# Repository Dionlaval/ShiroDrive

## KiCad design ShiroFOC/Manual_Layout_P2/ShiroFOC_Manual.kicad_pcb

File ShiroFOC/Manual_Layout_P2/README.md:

# ShiroFOC P2 — manual layout starting point

Open **ShiroFOC_Manual.kicad_pro** in this folder, then its PCB. This is the new working revision. The prior P1 project and Manual_Rebuild files are preserved.

## What is carried forward

- P1's 80 × 80 mm rounded outline, four M3 mounting holes, bulk-capacitor row and parallel bridge/phase-output arrangement.
- Latest manual schematic and imported component libraries. U604 now uses standard SOT-23-6 with its generic model (TI DBV six-pin package, 0.95 mm pitch; standard KiCad lands are an IPC-style alternative to TI's example).
- Current footprint and net assignments, including the LR2512D Kelvin shunts. Source-reference changes such as U301 → U4 and Q401/Q402/Q403 → U1/U2/U3 are explicitly mapped.
- Four copper layers: 70 / 17.5 / 17.5 / 70 µm. The copied dielectric dimensions are provisional; they are not a confirmed fabrication stack or an impedance calculation.

This is **rough placement, intentionally unrouted**. Component shifts clear gross overlaps, not optimize every pin-local loop. Final placement, copper planes, routing, silkscreen and fabrication checks are the user's next steps. A guide box is not a copper zone or enforced keepout.

## Guide layers

| Layer | Content |
|---|---|
| Dwgs.User | Mechanical screw envelopes and routing reminders |
| User.1 | Bulk capacitors, three power cells and brake-stage regions |
| User.2 | Auxiliary supply, USB and external-interface regions |
| User.3 | MCU/analog area, centred underside encoder and sense-route direction hints |
| F.Fab / B.Fab | Component references and body outlines |

Hide the guide layers when they obstruct routing. Nothing on them is electrical copper.

## Placement and routing checklist

1. **Mechanics first:** retain the encoder centre on the back at (140,140) mm. The magnet is outside that face; no top-side central magnet void is required. Keep the MCU offset from the encoder to preserve space for underside decoupling. Check connector mating clearance and corner screw/washer envelopes; the circles show an 8 mm hardware envelope.
2. **Three repeated phase cells:** U1/U2/U3 line up with J1's U/V/W holes. Keep each VM ceramic → MOSFET pair → low-side shunt → ceramic ground loop short and broad. Respect the actual schematic: the three sets of local VM bypass capacitors return to GND. Do not copy older notes that put a capacitor above the shunt.
3. **Shunts:** active phase U/V/W shunts are R3/R1/R5 respectively, on the back near the power cells. Pads1/4 carry current; pads2/3 are the Kelvin pickup stubs. Route from the stubs as a close pair, away from phase/gate/brake switching nodes. Keep power pours from swallowing the stubs. Short direct force paths and multiple correctly sized vias are needed for backside shunts; there is no fixed amps-per-via guarantee.
4. **Gate drive:** finish placement around the actual U4 gate-driver pins before routing. Put R2/R4/R6 near the relevant GH gate pads. Pair the high-side drive with its source/phase return and low-side drive with its driver return. Bootstrap capacitors C4/C8/C12 are shown on the gate-driver sheet, between BOOTSTRAP1/2/3 and HS_RETURN_U/V/W. Place them at the driver pins. Route HS_RETURN directly to the corresponding MOSFET SH pad alongside the high-side gate trace; PHASE_U/V/W are separate high-current routes to the motor.
5. **Quiet measurement:** R417/R418/R419 and corresponding V/W networks, bias resistors and optional feedback capacitors belong close to their U4 amplifier pins. Use the underside of the MCU where useful, keeping clear of the encoder and hot power copper. Place VREF/VDDA filters and bypass capacitors close to their pins. Do not run main DC or brake return current through this area.
6. **Ground:** create substantially continuous GND planes on In1.Cu and In2.Cu. They provide signal return paths, not the sole motor-current conductor. Use broad outer-layer VM/GND paths for power. Stitch local decoupling grounds and signal layer transitions to the planes. Check both inner layers for accidental slots caused by via fields. A VM thermal via must not touch GND; likewise the source above each shunt is not GND.
7. **Brake:** keep the external resistor connector and chopper loop at the edge, away from the encoder. Finish Q501/U501 placement and gate loop before signal routing. Keep BRK_SW copper compact and sense the bus from a quieter pickup.
8. **Supplies:** current topology is VM → LMR36510/U201 + L201 → 10V → MPM3620A/U205 → 5V mux → 3V3 LDO. U4 uses external VCC; there is no L301 internal-switcher inductor. Finish capacitor placement at U201 and U205 first, then keep feedback resistors away from switching copper. U205's embedded footprint keepout remains present.
9. **Interfaces:** AS5047 uses dedicated SPI; BMI323 uses I2C. Keep both over continuous ground. Place external Hall protection/buffer and U604 sensor-power protector near J601; place their decouplers at their pins. CAN protection belongs at the connectors, with JP801 termination access. USB D+/D− should be short and paired; determine 90Ω geometry from a real stack before treating the saved width/gap as final.
10. **Comparison part:** R7 is the disconnected BVR4026 parked outside the outline. Compare it to the small shunts and then remove it before production exports. DNP/excluded-from-BOM does not remove its copper/paste from Gerbers.

## Saved routing presets

- Global copper clearance / minimum track width: 0.15 mm.
- Default logic: 0.25 mm track, 0.20 mm clearance.
- Analog: 0.20 mm track/clearance. Gate: 0.40 mm initial width. Logic power: 0.50 mm initial width.
- Power class: 0.50 mm clearance target; its 2 mm track width is a router convenience, **not a 25 A current-rating calculation**. Use purpose-sized copper.
- Through vias: 0.60 / 0.30 mm default; 0.45 / 0.20 mm compact. No blind/buried or microvia plan.
- Copper-to-edge: 0.50 mm. Drill spacing: 0.20 mm base; 0.45 mm for pairs involving component pads, with a retained explicit U901 thermal-via exception.
- Silkscreen: 1.0 mm minimum text / 0.15 mm stroke / 0.20 mm clearance. Imported library reference styling is not final production silkscreen.

See `review/` for the native ERC, unrouted-board DRC, footprint/pad-net validation and migration manifest. Those checks establish a usable starting project, not a finished-board release. Remaining fast-overcurrent-trip, thermal and shunt reflow-profile questions carry forward from the manual schematic review and firmware requirements.

## Known starting-state flags

See [open items](review/OPEN_ITEMS.md): U204's imported land pattern has 0.10 mm copper gaps, U901 has 0.15 mm thermal-via hole webs, and U205 has two NC/test symbol pins without footprint pads. These are recorded rather than hidden by relaxed rules. The board is ready for manual placement/routing work, not fabrication.

## Optional brake NTC — 27 September 2026

J502 is the new **bottom-side, left-edge** JST GH two-pin connector: **1 = NTC, 2 = GND**. Use an electrically insulated 10 kΩ-at-25°C probe on the external brake resistor; configure its actual temperature curve and rating. R511 is the 10 kΩ pull-up. R512/C505/D505 form the series filter and rail clamps beside U4 on the back. Keep the unfiltered probe net away from switching copper; route its dedicated ground back to the quiet ground plane, not through the brake-current return. No new routing has been added.

PC2 / U4 pad 11 is now `NTC_BRAKE` / ADC12_IN8. The status LED moved to PC15 / pad 5 with R304 = 2.2 kΩ; TP1021 is now labelled `STATUS_LED_N`. Existing footprint placement is preserved. Use the updated [firmware requirements](../requirements/FIRMWARE_REQUIREMENTS.md); old firmware that drives PC2 as an LED output is incompatible.

See [addition notes and checks](review/brake_ntc/README.md). `review/brake_ntc/before.zip` preserves the project files from before this addition. The older Manual_Rebuild project remains unchanged.

## Bootstrap return correction — 27 September 2026

The latest saved user placement is retained. C4/C8/C12 now appear on the gate-driver schematic sheet, connected between each BOOTSTRAP pin and its OUTx/SH return. `HS_RETURN_U/V/W` belong to the Gate class; `PHASE_U/V/W` belong to the Power class. Keep these PCB routes separate: they join inside the dual-MOSFET package. Capacitor values and footprints are unchanged.

The five NTC components also have corrected hierarchy paths and restored references J502/R511/R512/C505/D505. See [current verification](review/bootstrap_return/README.md).

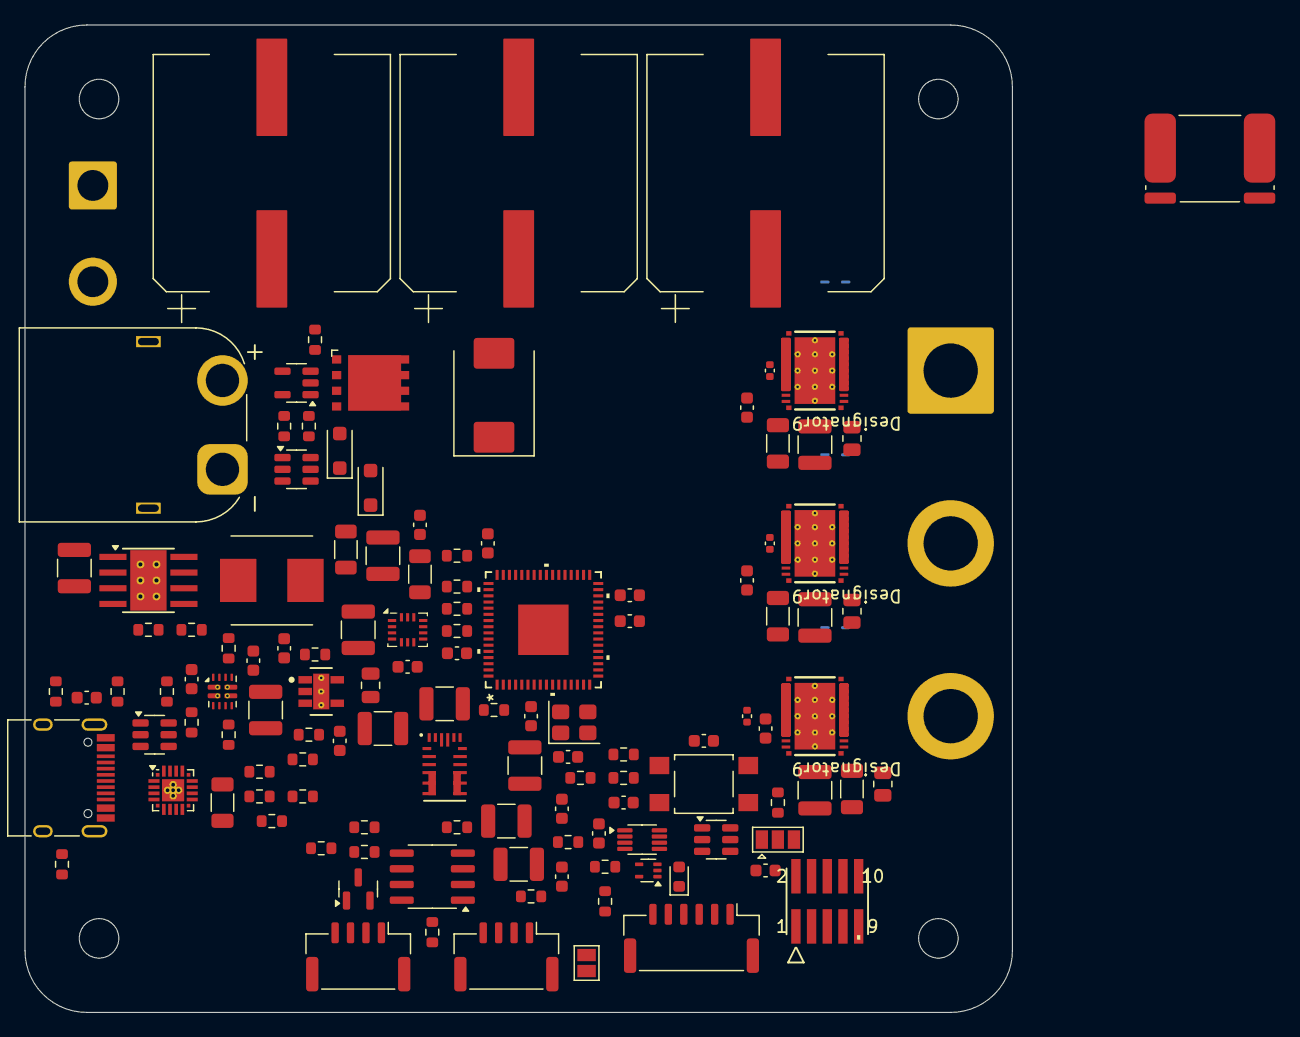
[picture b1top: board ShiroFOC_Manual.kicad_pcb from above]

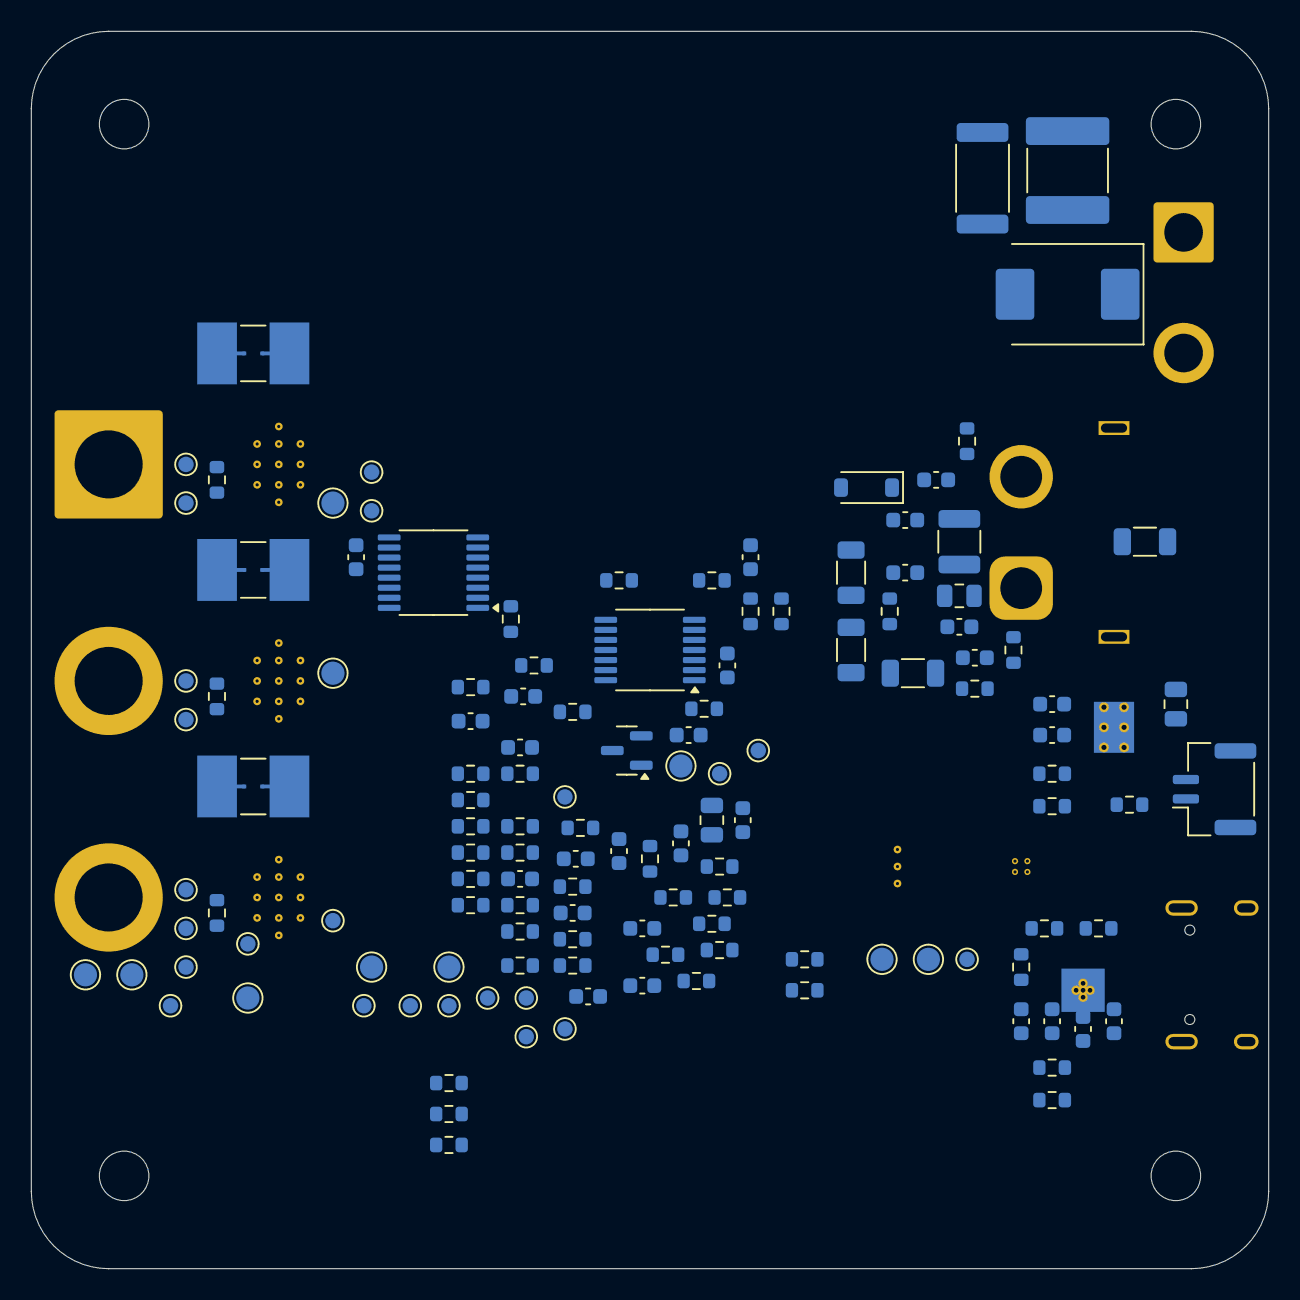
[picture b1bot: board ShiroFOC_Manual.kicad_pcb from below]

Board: 4 copper layers, 80.0 x 80.0 mm, 260 parts (132 on the bottom side), 145 nets, no tracks yet.

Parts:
C1, C5, C9: 10nF; C_0402_1005Metric
C2, C6, C10: 1uF; C_1206_3216Metric
C3, C7, C11: 4.7uF; C_1210_3225Metric
C4, C8, C12: 220nF; C_0603_1608Metric
C101, C102, C103: 680uF 63V; Panasonic_EEVFK_K16_18x16.5
C104: 4.7uF 100V X7R; C_1210_3225Metric
C105: 100nF 100V X7R; C_0805_2012Metric
C106: 10nF 100V C0G; C_0603_1608Metric
C107: RC DAMP C - TUNE; C_2220_5750Metric
C108, C314, C711, C712, C713: 10nF; C_0603_1608Metric
C201: 2.2uF 100V X7R; C_1210_3225Metric
C202: 220nF 100V X7R; C_0805_2012Metric
C203, C209, C211, C301, C303, C305, C307, C310, C601, C603, C605, C701, C702, C801, C902, C904: 100nF; C_0603_1608Metric
C204, C304, C306, C602, C802: 1uF; C_0603_1608Metric
C205, C206, C214, C215: 22uF 25V X7R; C_1210_3225Metric
C207: 4.7nF 2kV; C_1206_3216Metric
C208: 1uF 10V; C_0603_1608Metric
C210: 22uF 10V X7R; C_1210_3225Metric
C212, C213: 2.2uF 10V X7R; C_0603_1608Metric
C218, C219: 22uF 16V X7R; C_1210_3225Metric
C302: 10uF 10V; C_0805_2012Metric
C308, C309: 10pF C0G; C_0603_1608Metric
C311: 220nF 100V; C_0805_2012Metric
C312: 10uF 25V X7R; C_1210_3225Metric
C313: 100nF 25V; C_0603_1608Metric
C414, C424, C434: 47pF C0G; C_0603_1608Metric
C501: 1uF 25V; C_0603_1608Metric
C502, C503, C604: 100nF 50V; C_0603_1608Metric
C504: 1nF C0G; C_0603_1608Metric
C505: 100nF 16V; C_0603_1608Metric
C606: 4.7uF 16V X7R; C_0603_1608Metric
C607: 100nF 16V X7R; C_0603_1608Metric
C901, C903: 4.7uF 10V; C_0603_1608Metric
D101: VM TVS - SELECT AFTER TEST; D_SMC
D301: RED; LED_0603_1608Metric
D501: BZT52C12 12V; D_SOD-123
D502, D503: BAT54H; D_SOD-123F
D504: B5100C 100V 5A; D_SMC
D505: BAT54S; SOT-23
D601: TPD3E001DRLR 3-line ESD; TPD3E001_DRL5
D801: PESD2CANFD24V-T; SOT-23
H1, H2, H3, H4: M3 NPTH; MountingHole_3.2mm_M3
J1: MOTOR U/V/W; SolderWire-6sqmm_1x03_P14mm_D3.5mm_OD7mm
J101: AMASS XT60PW-M; AMASS_XT60PW-M_1x02_P7.20mm_Horizontal
J201: USB-C service; USB_C_Receptacle_HRO_TYPE-C-31-M-12
J501: BRAKE RESISTOR; SolderWire-2sqmm_1x02_P7.8mm_D2mm_OD3.9mm
J502: BRAKE NTC; JST_GH_SM02B-GHS-TB_1x02-1MP_P1.25mm_Horizontal
J601: EXT ENCODER / HALL; JST_GH_BM06B-GHS-TBT_1x06-1MP_P1.25mm_Vertical
J801: CAN 1; JST_GH_BM04B-GHS-TBT_1x04-1MP_P1.25mm_Vertical
J802: CAN 2; JST_GH_BM04B-GHS-TBT_1x04-1MP_P1.25mm_Vertical
J1001: ARM Cortex SWD 10-pin; FTSH_105_01_L_DV_K
JP601: SENSOR SUPPLY; SolderJumper-3_P1.3mm_Open_Pad1.0x1.5mm
JP801: TERM ENABLE; SolderJumper-2_P1.3mm_Open_Pad1.0x1.5mm
L201: 47uH / 1.9A; WE_LHMI_7050_74437349470
Q501: CSD19531Q5A 100V; CSD19531Q5A_Q5A_DQJ0008A
R1, R3, R5: 0.5m 1%; R_Shunt_LR2512D_0m5_3W_Kelvin
R2, R4, R6: 4R7; R_0805_2012Metric
R7: BVR 0.5m 1% (DNP); R_Shunt_Isabellenhuette_BVR4026
R101: 470k 0.25W; R_1206_3216Metric
R102: RC DAMP R - TUNE; R_2512_6332Metric
R103, R104: 270k 0.1% 100V; R_1206_3216Metric
R105: 27k 0.1%; R_0603_1608Metric
R106, R312, R711, R712, R713, R901: 1k; R_0603_1608Metric
R201: 100k 1%; R_0603_1608Metric
R202: 11.1k 1%; R_0603_1608Metric
R203, R204: 5.1k; R_0603_1608Metric
R205, R301, R302: 0R; R_0603_1608Metric
R206: 15.0k 1%; R_0603_1608Metric
R207, R209, R211, R213: 5.10k 1%; R_0603_1608Metric
R208: 10.0k 1%; R_0603_1608Metric
R210, R212: 22.0k 1%; R_0603_1608Metric
R214: 80.6k 1%; R_0603_1608Metric
R215, R305, R306, R307, R309, R311, R501, R504, R505, R604, R801, R805: 10k; R_0603_1608Metric
R216: 34.0k 0.1%; R_0603_1608Metric
R217: 6.49k 0.1%; R_0603_1608Metric
R218, R219, R303, R310, R615, R616, R617: 100k; R_0603_1608Metric
R304, R308, R715: 2.2k; R_0603_1608Metric
R313, R314: 22R; R_0603_1608Metric
R410, R420, R430, R441, R442, R443: 56k 0.1%; R_0603_1608Metric
R417, R418, R427, R428, R437, R438: 1k 0.1%; R_0603_1608Metric
R419, R429, R439: 28k 0.1%; R_0603_1608Metric
R502, R611: 33R; R_0603_1608Metric
R503: 4.7R; R_0603_1608Metric
R506, R507, R508: 150k 0.1% 200V; R_1206_3216Metric
R509: 12.7k 0.1%; R_0603_1608Metric
R510: 1M 0.1%; R_0603_1608Metric
R511: 10k 1%; R_0603_1608Metric
R512, R701, R702, R703: 4.7k 1%; R_0603_1608Metric
R605, R606, R607, R902, R903: 100R; R_0603_1608Metric
R608, R609, R610: 4.7k DNP; R_0603_1608Metric
R802: 120R 1%; R_0603_1608Metric
R803: 0R CANH link; R_0603_1608Metric
R804: 0R CANL link; R_0603_1608Metric
R904: 22.1k 1%; R_0603_1608Metric
R905: 47.5k 1%; R_0603_1608Metric
SW301: RESET; SW_SPST_TL3305A
TH701, TH702, TH703: 10k NTC B3380; R_0603_1608Metric
TP101: VM; TestPoint_Pad_D1.5mm
TP102: GND; TestPoint_Pad_D1.5mm
TP103: VBUS_SENSE; TestPoint_Pad_D1.5mm
TP201: PWR_SOURCE_STATUS; TestPoint_Pad_D1.5mm
TP202: 5V_USB; TestPoint_Pad_D1.5mm
TP301: VCC; TestPoint_Pad_D1.5mm
TP302: SCREF; TestPoint_Pad_D1.5mm
TP303: NRST; TestPoint_Pad_D1.5mm
TP501: BRAKE_GATE; TestPoint_Pad_D1.5mm
TP502: BRAKE_SWITCH; TestPoint_Pad_D1.5mm
TP701: NTC_PHASE_A; TestPoint_Pad_D1.0mm
TP702: NTC_PHASE_B; TestPoint_Pad_D1.0mm
TP703: NTC_PHASE_C; TestPoint_Pad_D1.0mm
TP901: USB_UART_TX; TestPoint_Pad_D1.0mm
TP902: USB_UART_RX; TestPoint_Pad_D1.0mm
TP1005: 5V_SYS; TestPoint_Pad_D1.0mm
TP1006: 3V3; TestPoint_Pad_D1.0mm
TP1008: SWDIO; TestPoint_Pad_D1.0mm
TP1009: SWCLK; TestPoint_Pad_D1.0mm
TP1010: ENC_SPI_CLK; TestPoint_Pad_D1.0mm
TP1011: SPI3_MISO; TestPoint_Pad_D1.0mm
TP1012: ENC_SPI_MOSI; TestPoint_Pad_D1.0mm
TP1013: FDCAN1_TX; TestPoint_Pad_D1.0mm
TP1014: FDCAN1_RX; TestPoint_Pad_D1.0mm
TP1015: FEEDBACK_A_H1; TestPoint_Pad_D1.0mm
TP1016: FEEDBACK_B_H2; TestPoint_Pad_D1.0mm
TP1018: OPO_U1; TestPoint_Pad_D1.0mm
TP1019: OPO_V1; TestPoint_Pad_D1.0mm
TP1020: OPO_W1; TestPoint_Pad_D1.0mm
TP1021: SPARE_GPIO_1; TestPoint_Pad_D1.0mm
TP1022: CAN_STB; TestPoint_Pad_D1.0mm
TP1023: EXT_SENSOR_FAULT_N; TestPoint_Pad_D1.0mm
TP1024: I2C2_SDA; TestPoint_Pad_D1.0mm
U1, U2, U3: CSD88599Q5DC; DMM0022A
U4: STSPIN32G4; QFN_IN32G4_STM
U201: LMR36510FADDAR; LMR36510_DDA
U202: USBLC6-2SC6; USBLC6_SOT23_6
U203: TPS2121RUXR; TPS2121_RUX
U204: TLV75533PDYDR; TLV75533_DYD_GND
U205: MPM3620AGQV-Z; IC18_MPM3620AGQV-Z_MNP
U501: UCC27517ADBVR; UCC27517A_DBV5
U502: TLV3012BIDBVR; SOT-23-6
U601: AS5047P-ATSM; AS5047P_TSSOP14
U602: TMUX1574PW; TMUX1574_PW16
U603: 74LVC3G17; VSSOP-8_2.3x2mm_P0.5mm
U604: TPS2553DBVR; SOT-23-6
U701: BMI323; BMI323_LGA14
U801: TCAN3413DR; SOIC-8_3.9x4.9mm_P1.27mm
U901: CP2102N-A02-GQFN20; SiliconLabs_QFN-20-1EP_3x3mm_P0.5mm_EP1.8x1.8mm_ThermalVias
Y301: 24MHz 7pF; Crystal_SMD_3225-4Pin_3.2x2.5mm

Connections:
3V3: C213.1, C301.1, C302.1, C307.1, C503.1, C601.1, C602.1, C603.1, C605.1, C701.1, C702.1, C801.1, C802.1, C901.1, C902.1, C903.1, C904.1, D505.2 (K), J1001.1, JP601.1 (A), R215.1, R301.1, R303.1, R304.1, R305.1, R308.1, R309.1, R310.1, R511.1, R604.1, R701.1, R702.1, R703.1, R715.1, R801.1, R805.1, R901.1, TP1006.1, U4.1 (REG3V3/VDD), U4.2 (VBAT), U4.64 (REGIN), U204.5 (OUT), U502.6 (VDD), U601.11 (VDD), U601.12 (VDD3V3), U602.16 (VDD), U603.8 (VCC), U701.5 (VDDIO), U701.8 (VDD), U701.12 (CSB), U801.3 (VCC), U801.5 (VIO), U901.6 (VDD), U901.7 (VREGIN)
5V_BAT: C218.1, C219.1, R206.1, R210.1, R216.1, U203.7 (IN1), U205.7 (OUT), U205.8 (OUT), U205.9 (OUT)
5V_SYS: C210.1, C211.1, C212.1, JP601.3 (B), TP1005.1, U203.1 (OUT), U203.8 (OUT), U204.1 (IN), U204.3 (EN)
5V_USB: C208.1, R205.2, R208.1, R212.1, TP202.1, U203.2 (IN2)
5V_USB_RAW: J201.A4 (VBUS), J201.A9 (VBUS), J201.B4 (VBUS), J201.B9 (VBUS), R205.1, R904.1, U202.5 (VBUS)
/5 V / 3.3 V power/10V_FB: R201.2, R202.1, U201.5 (FB)
/5 V / 3.3 V power/10V_GOOD: R218.2, R219.1, U201.4 (PG), U205.17 (EN)
/5 V / 3.3 V power/U205_AGND: R217.2, U205.3 (AGND)
/5 V / 3.3 V power/U205_SW: U205.4 (SW), U205.5 (SW), U205.6 (SW)
/Brake chopper/BRAKE_NTC_RAW: J502.1, R511.2, R512.1
/Brake chopper/BRAKE_OV_CMD: D503.2 (A), R510.1, U502.1 (OUT)
/Brake chopper/BRAKE_PWM_DRV: D502.1 (K), D503.1 (K), R505.1, U501.3 (IN+)
/CAN interface/CANH_BUS: D801.1 (CANH_IN), J801.3, J802.3, R802.1, R803.2
/CAN interface/CANH_INT: R803.1, U801.7 (CANH)
/CAN interface/CANL_BUS: D801.2 (CANL_IN), J801.2, J802.2, JP801.2, R804.2
/CAN interface/CANL_INT: R804.1, U801.6 (CANL)
/CAN interface/CAN_SHIELD: J801.4, J802.4
/CAN interface/CAN_TERM_MID: JP801.1, R802.2
/Current / temperature/NTC_A_RAW: R701.2, R711.1, TH701.1
/Current / temperature/NTC_B_RAW: R702.2, R712.1, TH702.1
/Current / temperature/NTC_C_RAW: R703.2, R713.1, TH703.1
/Current / temperature/OPN_U1: C414.2, R418.2, R419.2, U4.16 (-)
/Current / temperature/OPN_V1: C424.2, R428.2, R429.2, U4.22 (-)
/Current / temperature/OPN_W1: C434.2, R438.2, R439.2, U4.25 (-)
/Current / temperature/OPP_U1: R410.2, R417.2, R441.1, U4.14 (+)
/Current / temperature/OPP_V1: R420.2, R427.2, R442.1, U4.20 (+)
/Current / temperature/OPP_W1: R430.2, R437.2, R443.1, U4.23 (+)
/External feedback/EXT_SUPPLY_SELECTED: C606.1, JP601.2 (C), U604.1 (IN), U604.3 (EN), U604.5 (ILIM)
/External feedback/EXT_VCC: C607.1, J601.1, R608.1, R609.1, R610.1, U604.6 (OUT)
/External feedback/FB_ESD_RAIL: C604.1, D601.5 (VCC)
/MCU / clock / SWD/NRST: C310.1, J1001.10, R303.2, SW301.1, TP303.1, U4.8 (PG10/NRST)
/MCU / clock / SWD/STATUS_LED_N: D301.1 (K), TP1021.1, U4.5 (PC15)
/USB service/CP2102_RST_N: R901.2, U901.9 (RST)
/USB service/CP2102_VBUS_SENSE: R904.2, R905.1, U901.8 (VBUS)
/USB service/UART_BRIDGE_RX: R903.2, U901.17 (RXD)
/USB service/UART_BRIDGE_TX: R902.1, U901.18 (TXD)
/USB service/USB_CC1: J201.A5 (CC1), R203.1
/USB service/USB_CC2: J201.B5 (CC2), R204.1
/USB service/USB_DM: U202.6 (IO1), U901.5 (D-)
/USB service/USB_DM_CONN: J201.A7 (D-), J201.B7 (D-), U202.1 (IO1)
/USB service/USB_DP: U202.4 (IO2), U901.4 (D+)
/USB service/USB_DP_CONN: J201.A6 (D+), J201.B6 (D+), U202.3 (IO2)
/USB service/USB_SHIELD: C207.1, J201.S1 (SHIELD)
AS5047P_CS_N: R309.2, U4.51 (PA15), U601.1 (CSn)
BOOTSTRAP1: C4.2, U4.41 (BOOTSTRAP1)
BOOTSTRAP2: C8.2, U4.38 (BOOTSTRAP2)
BOOTSTRAP3: C12.2, U4.35 (BOOTSTRAP3)
BRAKE_PWM: R501.1, R502.1, U4.60 (PB9)
CAN_STB: R801.2, TP1022.1, U4.28 (PB10), U801.8 (STB)
EXT_FEEDBACK_SELECT: R306.1, U4.53 (PD2), U602.1 (SEL)
EXT_SENSOR_FAULT_N: R604.2, TP1023.1, U4.3 (PC13), U604.4 (~FAULT)
FDCAN1_RX: TP1014.1, U4.47 (PA11), U801.4 (RXD)
FDCAN1_TX: R805.2, TP1013.1, U4.48 (PA12), U801.1 (TXD)
FEEDBACK_A_H1: TP1015.1, U4.57 (PB6), U602.4 (D1)
FEEDBACK_B_H2: TP1016.1, U4.58 (PB7), U602.7 (D2)
FEEDBACK_I_H3: R307.1, U4.59 (PB8/BOOT0), U602.9 (D3)
GHS1: R2.2, U4.43 (GHS1)
GHS2: R4.2, U4.40 (GHS2)
GHS3: R6.2, U4.37 (GHS3)
GLS1: U1.22 (GL), U4.29 (GLS1)
GLS2: U2.22 (GL), U4.30 (GLS2)
GLS3: U3.22 (GL), U4.31 (GLS3)
GND: C1.2, C2.2, C3.2, C5.2, C6.2, C7.2, C9.2, C10.2, C11.2, C101.2, C102.2, C103.2, C104.2, C105.2, C106.2, C107.2, C108.2, C201.2, C202.2, C204.2, C205.2, C206.2, C207.2, C208.2, C209.2, C210.2, C211.2, C212.2, C213.2, C214.2, C215.2, C218.2, C219.2, C301.2, C302.2, C303.2, C304.2, C305.2, C306.2, C307.2, C308.2, C309.2, C310.2, C311.2, C312.2, C313.2, C314.2, C501.2, C502.2, C503.2, C504.2, C505.2, C601.2, C602.2, C603.2, C604.2, C605.2, C606.2, C607.2, C701.2, C702.2, C711.2, C712.2, C713.2, C801.2, C802.2, C901.2, C902.2, C903.2, C904.2, D101.2 (A), D501.2 (A), D505.1 (A), D601.3 (GND), D801.3 (GND), J101.1, J201.A1 (GND), J201.A12 (GND), J201.B1 (GND), J201.B12 (GND), J502.2, J601.2, J801.1, J802.1, J1001.3, J1001.5, J1001.9, Q501.1 (S), Q501.2 (S), Q501.3 (S), R1.4 (POWER-), R3.4 (POWER-), R5.4 (POWER-), R101.2, R105.2, R202.2, R203.2, R204.2, R207.2, R209.2, R211.2, R213.2, R214.2, R219.2, R306.2, R307.2, R311.2, R441.2, R442.2, R443.2, R501.2, R504.2, R505.2, R509.2, R615.2, R616.2, R617.2, R905.2, SW301.2, TH701.2, TH702.2, TH703.2, TP102.1, U4.32 (PGND), U4.65 (VSS/EP), U201.1 (PGND), U201.9 (GND), U202.2 (GND), U203.12 (GND), U204.2 (GND), U205.12 (PGND), U205.13 (PGND), U205.14 (PGND), U501.2 (GND), U501.4 (IN-), U502.2 (GND), U601.5 (TEST), U601.13 (GND), U602.2 (S1A), U602.5 (S2A), U602.8 (GND), U602.11 (S3A), U603.4 (GND), U604.2 (GND), U701.1 (SDO/SA0), U701.6 (GNDIO), U701.7 (GND), U801.2 (GND), U901.3 (GND), U901.12 (GND), U901.21 (EP), Y301.2, Y301.4
I2C2_SCL: R308.2, U4.21 (PC4), U701.13 (SCK/SCL)
I2C2_SDA: R715.2, TP1024.1, U4.44 (PA8), U701.14 (SDI/SDA)
IMU_INT1: U4.17 (PA4), U701.4 (INT1)
IMU_INT2: U4.18 (PA5), U701.9 (INT2)
INPUT_MUX_ENABLE_N: R305.2, U4.4 (PC14), U602.15 (EN_N)
NTC_BRAKE: C505.1, D505.3 (COM), R512.2, U4.11 (PC2)
NTC_PHASE_A: C711.1, R711.2, TP701.1, U4.12 (PC3)
NTC_PHASE_B: C712.1, R712.2, TP702.1, U4.9 (PC0)
NTC_PHASE_C: C713.1, R713.2, TP703.1, U4.10 (PC1)
unnamed: C107.1, R102.2
unnamed: D301.2 (A), R304.2
unnamed: D501.1 (K), Q501.4 (G), R503.2, R504.1, TP501.1
unnamed: D502.2 (A), R502.2
unnamed: D504.2 (A), J501.2, Q501.5 (D), Q501.6 (D), Q501.7 (D), Q501.8 (D), TP502.1
unnamed: D601.1 (IO1), J601.3, R605.1
unnamed: D601.2 (IO2), J601.4, R606.1
unnamed: D601.4 (IO3), J601.5, R607.1
unnamed: R1.1 (POWER+), U2.12 (PGND), U2.13 (PGND), U2.14 (PGND), U2.15 (PGND), U2.16 (PGND), U2.17 (PGND), U2.18 (PGND), U2.19 (PGND), U2.20 (PGND)
unnamed: R3.1 (POWER+), U1.12 (PGND), U1.13 (PGND), U1.14 (PGND), U1.15 (PGND), U1.16 (PGND), U1.17 (PGND), U1.18 (PGND), U1.19 (PGND), U1.20 (PGND)
unnamed: R5.1 (POWER+), U3.12 (PGND), U3.13 (PGND), U3.14 (PGND), U3.15 (PGND), U3.16 (PGND), U3.17 (PGND), U3.18 (PGND), U3.19 (PGND), U3.20 (PGND)
unnamed: R103.2, R104.1
unnamed: R104.2, R105.1, R106.1
unnamed: R310.2, R311.1, R312.1
unnamed: R506.2, R507.1
unnamed: R507.2, R508.1
unnamed: R605.2, R608.2, R615.1, U603.1
unnamed: R606.2, R609.2, R616.1, U603.3
unnamed: R607.2, R610.2, R617.1, U603.6
unnamed: R2.1, U1.1 (GH)
unnamed: C4.1, U1.2 (SH)
unnamed: R4.1, U2.1 (GH)
unnamed: C8.1, U2.2 (SH)
unnamed: R6.1, U3.1 (GH)
unnamed: C12.1, U3.2 (SH)
unnamed: J1001.2, TP1008.1, U4.49 (PA13/SWDIO)
unnamed: J1001.4, TP1009.1, U4.50 (PA14/SWCLK)
unnamed: C308.1, U4.6 (PF0), Y301.1
unnamed: C309.1, U4.7 (PF1), Y301.3
unnamed: C314.1, R312.2, TP302.1, U4.52 (SCREF)
unnamed: C203.1, U201.7 (BOOT)
unnamed: C203.2, L201.1, U201.8 (SW)
unnamed: C204.1, U201.6 (VCC)
unnamed: R208.2, R209.1, U203.3 (CP2)
unnamed: R214.1, U203.10 (ILM)
unnamed: R210.2, R211.1, U203.5 (OV1)
unnamed: R212.2, R213.1, U203.4 (OV2)
unnamed: R206.2, R207.1, U203.6 (PR1)
unnamed: C209.1, U203.11 (SS)
unnamed: R216.2, R217.1, U205.1 (FB)
unnamed: R503.1, U501.5 (OUT)
unnamed: C504.1, R508.2, R509.1, R510.2, U502.3 (IN+)
unnamed: U502.4 (IN-), U502.5 (REF)
unnamed: R313.2, TP1010.1, U601.2 (CLK)
unnamed: R611.1, U601.3 (MISO)
unnamed: R314.2, TP1012.1, U601.4 (MOSI)
unnamed: U602.3 (S1B), U603.7
unnamed: U602.6 (S2B), U603.5
unnamed: U602.10 (S3B), U603.2
OPO_U1: C414.1, R419.1, TP1018.1, U4.15 (OUT)
OPO_V1: C424.1, R429.1, TP1019.1, U4.19 (OUT)
OPO_W1: C434.1, R439.1, TP1020.1, U4.24 (OUT)
OUT1: J1.1 (U), U1.3 (VSW), U1.4 (VSW), U1.5 (VSW), U1.6 (VSW), U1.7 (VSW), U1.8 (VSW), U1.9 (VSW), U1.10 (VSW), U1.11 (VSW), U4.42 (OUT1)
OUT2: J1.2 (V), U2.3 (VSW), U2.4 (VSW), U2.5 (VSW), U2.6 (VSW), U2.7 (VSW), U2.8 (VSW), U2.9 (VSW), U2.10 (VSW), U2.11 (VSW), U4.39 (OUT2)
OUT3: J1.3 (W), U3.3 (VSW), U3.4 (VSW), U3.5 (VSW), U3.6 (VSW), U3.7 (VSW), U3.8 (VSW), U3.9 (VSW), U3.10 (VSW), U3.11 (VSW), U4.36 (OUT3)
PWR_SOURCE_STATUS: R215.2, TP201.1, U203.9 (ST)
SHUNT_U_SENSE_N: R3.3 (SENSE-), R418.1
SHUNT_U_SENSE_P: R3.2 (SENSE+), R417.1
SHUNT_V_SENSE_N: R1.3 (SENSE-), R428.1
SHUNT_V_SENSE_P: R1.2 (SENSE+), R427.1
SHUNT_W_SENSE_N: R5.3 (SENSE-), R438.1
SHUNT_W_SENSE_P: R5.2 (SENSE+), R437.1
SPI3_MISO: R611.2, TP1011.1, U4.55 (PB4)
SPI3_MOSI_MCU: R314.1, U4.56 (PB5)
SPI3_SCK_MCU: R313.1, U4.54 (PB3)
USB_UART_RX: R902.2, TP902.1, U4.46 (PA10)
USB_UART_TX: R903.1, TP901.1, U4.45 (PA9)
VBUS_MUX_IN: R106.2, U602.13 (S4A), U602.14 (S4B)
VBUS_SENSE: C108.1, TP103.1, U4.13 (PA0), U602.12 (D4)
VCC: C205.1, C206.1, C214.1, C215.1, C312.1, C313.1, C501.1, C502.1, L201.2, R201.1, R218.1, TP301.1, U4.63 (VCC), U205.16 (IN), U501.1 (VDD)
VDDA: C303.1, C304.1, R301.2, R302.1, U4.27 (VDDA)
VM: C1.1, C2.1, C3.1, C5.1, C6.1, C7.1, C9.1, C10.1, C11.1, C101.1, C102.1, C103.1, C104.1, C105.1, C106.1, C201.1, C202.1, C311.1, D101.1 (K), D504.1 (K), J101.2, J501.1, R101.1, R102.1, R103.1, R506.1, TP101.1, U1.27 (VIN), U2.27 (VIN), U3.27 (VIN), U4.61 (VM), U4.62 (SW), U201.2 (VIN), U201.3 (EN)
VREF+: C305.1, C306.1, R302.2, R410.1, R420.1, R430.1, U4.26 (VREF+)

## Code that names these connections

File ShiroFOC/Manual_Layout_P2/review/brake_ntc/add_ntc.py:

from pathlib import Path
import sys,copy,json,zipfile,hashlib,math
sys.path.insert(0,'/tmp/cascade_work')
from edit import *
P=Path(__file__).resolve().parents[2];OUT=P/'review/brake_ntc';S=Path('/Applications/KiCad/KiCad.app/Contents/SharedSupport/symbols')
backup=OUT/'before.zip'
assert not backup.exists(),'Already applied; do not rerun'
paths=list(P.glob('*.kicad_sch'))+[P/'ShiroFOC_Manual.kicad_pcb',P/'ShiroFOC_Manual.kicad_pro',P/'libs/Manual.kicad_sym',P.parent/'requirements/FIRMWARE_REQUIREMENTS.md']
with zipfile.ZipFile(backup,'w',zipfile.ZIP_DEFLATED) as z:
 for path in paths:z.write(path,str(path.relative_to(P.parent)))
(OUT/'before_hashes.json').write_text(json.dumps({str(x):hashlib.sha256(x.read_bytes()).hexdigest() for x in paths},indent=2))
# Change the functional-symbol pin types consistently in the project library and every embedded copy.
def pin_types(lib):
 for unit in children(lib,'symbol'):
  for pin in children(unit,'pin'):
   num=one(pin,'number')[1]
   if num=='11':pin[1]='input'
   elif num=='5':pin[1]='output'
for path in P.glob('*.kicad_sch'):
 d=read(path);changed=False
 for lib in children(one(d,'lib_symbols') or [],'symbol'):
  if lib[1]=='Manual:STSPIN32G4_Functional':pin_types(lib);changed=True
 if changed:write(path,d)
lp=P/'libs/Manual.kicad_sym';d=read(lp)
for lib in children(d,'symbol'):
 if lib[1]=='STSPIN32G4_Functional':pin_types(lib)
write(lp,d)
def wire(d,a,b):
 d.append(['wire',['pts',['xy',*map(str,a)],['xy',*map(str,b)]],['stroke',['width','0'],['type','default']],['uuid',uid()]])
def label(d,name,xy,glob=False,angle=0):
 x=['global_label' if glob else 'label',Q(name)]
 if glob:x.append(['shape','bidirectional'])
 x += [['at',*map(str,xy),str(angle)],['effects',['font',['size','1.016','1.016']],['justify','left' if angle==0 else 'right']+([] if glob else ['bottom'])],['uuid',uid()]]
 d.append(x)
def text(d,t,xy,size=1.27):d.append(['text',Q(t),['at',*map(str,xy),'0'],['effects',['font',['size',str(size),str(size)]],['justify','left','top']],['uuid',uid()]])
def junction(d,xy):d.append(['junction',['at',*map(str,xy)],['diameter','0'],['color','0','0','0','0'],['uuid',uid()]])
# Relocate the existing LED drawing into the free right-hand area; physical LED placement unchanged.
p=P/'MCUclockSWD.kicad_sch';d=read(p)
for refname in ['D301','R304','#PWR03Controller8']:shift(ref(d,refname),116.84,0)
for w in list(children(d,'wire')):
 pts=[tuple(map(float,x[1:])) for x in children(one(w,'pts'),'xy')]
 if pts==[(163.83,99.06),(175.26,99.06)]:d.remove(w)
 elif pts in [[(185.42,99.06),(201.93,99.06)],[(212.09,92.71),(212.09,99.06)]]:shift(w,116.84,0)
for l in children(d,'label'):
 if l[1]=='SPARE_GPIO_1':l[1]=Q('STATUS_LED_N')
wire(d,(283.21,99.06),(292.1,99.06));label(d,'STATUS_LED_N',(283.21,99.06))
wire(d,(163.83,99.06),(179.07,99.06));label(d,'NTC_BRAKE',(179.07,99.06),True)
text(d,'STATUS LED: PC15, active low / open drain.\nR304 limits LED sink current; keep LSE disabled.\nPC2 is now ADC12_IN8 for the external brake NTC.',(279.4,109.22),1.016)
# 2.2k bounds LED current below 1.65mA even with a shorted LED, leaving room for PC14.
update(ref(d,'R304'),'Value','2.2k');pr=prop(ref(d,'R304'),'Procurement')
if pr:pr[2]=Q('2.2k 1%, 0603; low-current active-low status LED')
write(p,d)
# New block on brake sheet.
p=P/'07_Brake_Chopper.kicad_sch';d=read(p);libstore=one(d,'lib_symbols');root=one(read(P/'ShiroFOC_Manual.kicad_sch'),'uuid')[1];sheet=one(d,'uuid')[1]
def std(lib,name):
 id=lib+':'+name
 if not any(x[1]==id for x in children(libstore,'symbol')):
  x=copy.deepcopy(next(x for x in children(read(S/(lib+'.kicad_sym')),'symbol') if x[1]==name));assert not one(x,'extends');x[1]=Q(id);libstore.append(x)
 return id
new=[]
def component(lib,name,r,v,xy,fp,angle=0,mpn='',ds=''):
 id=std(lib,name);x=['symbol',['lib_id',Q(id)],['at',*map(str,xy),str(angle)],['unit','1'],['in_bom','yes'],['on_board','yes'],['dnp','no'],['uuid',uid()]]
 for key,value,offset,hide in [('Reference',r,-5.08,False),('Value',v,-2.54,False),('Footprint',fp,0,True),('Datasheet',ds,0,True),('MPN',mpn,0,True)]:
  x.append(['property',Q(key),Q(value),['at',str(xy[0]+(5.08 if name in ['R','C'] and angle==0 else 0)),str(xy[1]+offset),'0'],['effects',['font',['size','1.016','1.016']]]+([['hide','yes']] if hide else [])])
 x.append(['instances',['project',Q('ShiroFOC_Manual'),['path',Q('/'+root+'/'+sheet),['reference',Q(r)],['unit','1']]]]);d.append(x);new.append({'ref':r,'footprint':fp,'uuid':one(x,'uuid')[1],'sheet':sheet});return x
# connector rotated 180: pin1 at x+5.08,y; pin2 at x+5.08,y-2.54
component('Connector_Generic','Conn_01x02','J502','BRAKE NTC',(218.44,212.09),'Connector_JST:JST_GH_SM02B-GHS-TB_1x02-1MP_P1.25mm_Horizontal',180,'SM02B-GHS-TB(LF)(SN)')
component('Device','R','R511','10k 1%',(241.3,198.12),'Resistor_SMD:R_0603_1608Metric')
component('Device','R','R512','4.7k 1%',(266.7,212.09),'Resistor_SMD:R_0603_1608Metric',90)
component('Device','C','C505','100nF 16V',(289.56,224.79),'Capacitor_SMD:C_0603_1608Metric')
component('Diode','BAT54S','D505','BAT54S',(320.04,212.09),'Package_TO_SOT_SMD:SOT-23',90,'BAT54S,215','https://assets.nexperia.com/documents/data-sheet/BAT54S.pdf')
# 3V3 divider -> series resistor -> filtered/clamped ADC. BAT54S rotated90:1bottom(GND),2top(3V3),3right(signal).
for a,b in [((223.52,212.09),(241.3,212.09)),((241.3,212.09),(262.89,212.09)),((241.3,201.93),(241.3,212.09)),((241.3,190.5),(241.3,194.31)),((270.51,212.09),(289.56,212.09)),((289.56,212.09),(289.56,220.98)),((289.56,228.6),(289.56,232.41)),((289.56,212.09),(297.18,212.09)),((297.18,212.09),(297.18,236.22)),((297.18,236.22),(332.74,236.22)),((332.74,236.22),(332.74,212.09)),((325.12,212.09),(332.74,212.09)),((332.74,212.09),(347.98,212.09)),((320.04,204.47),(320.04,190.5)),((320.04,219.71),(320.04,232.41)),((223.52,209.55),(228.6,209.55)),((228.6,209.55),(228.6,232.41))]:wire(d,a,b)
for xy in [(241.3,212.09),(289.56,212.09),(332.74,212.09)]:junction(d,xy)
label(d,'NTC_BRAKE',(347.98,212.09),True)
label(d,'BRAKE_NTC_RAW',(241.3,212.09))
# Existing project power symbols, cloned into sheet.
for template,r,xy in [('#PWR05BrakeChopper10','#PWR_BRAKE_NTC_1',(241.3,190.5)),('#PWR05BrakeChopper10','#PWR_BRAKE_NTC_2',(320.04,190.5)),('#PWR05BrakeChopper9','#PWR_BRAKE_NTC_3',(228.6,232.41)),('#PWR05BrakeChopper9','#PWR_BRAKE_NTC_4',(289.56,232.41)),('#PWR05BrakeChopper9','#PWR_BRAKE_NTC_5',(320.04,232.41))]:d.append(clone(ref(d,template),r,xy))
for t in children(d,'text'):
 if t[1]=='Internal 1.242 V reference returns directly to IN−.':one(t,'at')[1:3]=['25.4','231.14']
 elif t[1]=='The positive-feedback resistor is wired back to IN+.':one(t,'at')[1:3]=['25.4','224.79']
text(d,'OPTIONAL EXTERNAL BRAKE-RESISTOR TEMPERATURE',(210.82,180.34),1.27)
text(d,'10k NTC at 25C; configure the actual probe curve in firmware.\nJ502: 1 = NTC, 2 = GND. Probe insulated from resistor power terminals.',(210.82,168.91),1.016)
text(d,'Open = high; short = low. Filter/clamps at MCU; twist probe pair.\nThermal warning/derating only: do not disable hardware bus clamp on overtemperature.',(190.5,271.78),1.016)
write(p,d)
(OUT/'new_components.json').write_text(json.dumps(new,indent=2));print('Added brake NTC schematic block; PC2 ADC / PC15 LED remap; five PCB components')
